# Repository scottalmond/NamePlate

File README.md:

# Name Plate Overview

Many cubicles are adorned with a standard aluminum name plate holding a piece of paper denoting the occupant's name.  This project presents an upgraded name tag that is backlit with LEDs.

This project was started as something simple to get active again after the COVID-19 lockdown.  Intent was to produce a visually engaging product with a price point at or below $25 in small production runs (10 units) to be in compliance with corporate gifting guidelines.

This unit employs nominally 100 WS2812B "NeoPixel" RGBW LEDs.  An ATtiny3216 was selected as a well supported processor (Arduino IDE) with a sizable flash memory (32kB).  To keep the design margin large, the SOIC package was selected.

The user can adjust the brightness of the unit through a potentiometer.  A Periphreal Touch Controller button allows quick user input while a hall effect sensor allows administrative functions.  A DIP switch allows for operation mode selection

# Assembled Unit

# Constituent Components

## Bill of Materials

## PCB

## Case

## Display Mask

## Face Plate

## Programmer

Direct referenced from: http://www.technoblogy.com/show?2OCH

- Install ElTangas's jtag2updi on Arduino Uno, Duemilanova or equivalent ATmega328p.  -- Details for making UPDI programmer: https://github.com/SpenceKonde/megaTinyCore/blob/master/MakeUPDIProgrammer.md
-- Use pin PD6 for UPDI I/O
- Install Spence Konde's megaTinyCore in the Arduino IDE
-- Instructions: https://github.com/SpenceKonde/megaTinyCore/blob/master/Installation.md
-- add to additional board URLs: http://drazzy.com/package_drazzy.com_index.json
-- boards manager add: "megaTinyCore" v2.0.5
- Upload settings:
-- Processor: ATtiny3216
-- 4.2 V BOD
-- 16 MHz
-- Programmer: jtag2updi

J8:
Pin 1: UPDI
Pin 2: +5V
Pin 6: GND

## Processor

doc: http://ww1.microchip.com/downloads/en/DeviceDoc/ATtiny3216-17-DataSheet-DS40002205A.pdf

# Periphreals

## DC Power

Note that this unit can sink substancial current.  It is recommended to power the unit with a 5V USB adapter capable of sourcing 2 Amps or more.

## LEDs [PA7]

## Touch Button [PB0]

Touching and releasing the very upper-left corner of the device for nominally 0.5 seconds will register a tap.  The unit will transition  between display patterns.

## Hall effect sensor [PA3]

Place a fridge or hard drive magnet just above the USB port.  This will activate <TBD function - implemented as fallback if PTC was problematic>

## Brightness Potentiometer [PA2]

Uncover the circuit board by removing the two thumb screws on either side of the faceplate.  Rotate the Philips potentiometer at the bottom left of the unit CW (?) to increase brightness.

## DIP Switch Settings [PA6, PA5, PA4]

Position 1:
Set to "OFF" to allow the displayed pattern to automaically update daily.  Set to "ON" to hold the currrently displayed pattern indefinitely.

Position 2:
Set to "ON" to configure the unit for collaboration mode.  In this mode the unit will communicate with other circuit boards to coordinate the displayed pattern.  For single PCB operation, the normal operation mode is "OFF".

Position 3:
Set to "ON" to enable diagnostic mode to allow verification and troublshooting of the user interfaces and outputs.  "OFF" is normal device operation.

Position 4:
Set to "ON" to connect the ID pin of the microUSB port to to the UPDI pin on the micro controller.  This is used for programming of the device without removing the circuit board from the casing.  "OFF" is normal operation.

# Collaboration Mode [PxD: PB2, RxD: PB3]

Multiple PCBs can be linked together to produce a larger display.  
<TBR>

# TODO

Add area for writing in owner name on PCB, for tracking units through development (if code differs)
Add CC BY 4.0 license to schematic
add year produced to PCB
>>> allow for batteyr power and power switch
>>> consider accel and swinging unit to create persistence of vision text display
add schematic links to readme.md
get solder paste with thinner tip
*** move micro USB header - difficult to reach for rework with config switches behind it (layout design issue)
note: LED is N/C in layout - why not flagged in DRc...?
b/c omitted connection in schematic due to copy-paste omission...
***fix D60 connection to 5V in next rev (schematic DRC issue)
-- run DRC in schematic too...
note: screw reads ~4V on delivery
magnet stuck at 0.87V despite exposure to hard drive magnet...
tried with pullup, still rigid at 0.87V
part is hot to the touch
note, the schematic part is AH1806 (hall switch) which has different pinout
- used this footprint because no footprint was supplied by vendor
*** next rev to swap pins 2 and 3 (schematic footprint issue)
consider testability point for EVERY IO
in user guide, include diagrams of expected UI screen output, ref 11.7V battery charger manual
include build number in start up script
compare findings on this CCA vs pendant which had button rotate 90 degrees (schematic footprint issue) and traces too close to holes (layout issue)
consider swapping hall effect sensor and brightness - allow greater accessibility to magnetic input
note:0.37" from LED-surface to top of programming header [note: 0.38" per data sheet, erxcluding solder]
contiguous undervolt - dim screen brighntess (LiPo response to dropping voltage)
min stackup (NO 1/16" acry): pcb 1.6 mm/0.063", 100 mil UPDI: 0.37", 0.125" acrylic face, 0.05" margin: 0.608"
max stackup (NO 1/16" acry): [5 turns 4-40 is 0.1250"] [50 mil backing], 200 mil standoff, 0.608" from above: 0.808"
min w/ 1/16 acry: 0.63+ above = 0.671"
max w/ 1/16 acry: 0.63+ above = 0.871"
note: thumb screw head 11/64" thick BEYOND base length above
0.75" is max length fully threaded.  next step up is 1"
note: head diameter on thumb screw is 5/16"
.75-1/8"+.05 back = 
box height at 0.8".  Add 1/16" when fabricating with acrylic
>>> enlarge PCB holes to be close fit.  Currently too small
allow for flipping vertically - flip flag, matrix rtain, etc
>>> consider moving silk screen contact info to behind a hole in the back of the unit
v1-0 --> v1-1 case:
50 mil WAS --> 100 mil IS margin inside pcb-to-case
50 mil WAS --> 150 mil IS wall thickness
WAS circle vent holes --> IS diamond vent holes --> will turn off supports
WAS 4x PCB holders, IS 2x PCB holders in the center
WAS NO chamfer inside unit --> IS chamfer around inner edge to provide wall support
WAS 4x faceplate holders --> IS NO facaeplate holders
WAS NO USB port --> IS USB PORT --> need dimensions of usb plug, and concern with unsupported 3d print
micro usb header metal = 0.07", 0.2" from opposing side of usb to verrtical case edge, 0.31" total
0.27" wide, 0.35" from opposing edge to case, 0.43" total
kicad center hole at 3.8" Y, 4.083" for microUSB port center
microUSB center 1.2 mm above surface of PCB
consider first boot (all 1's in EEPROM) to debug chaper.  First user input to change EEPROM exits hidden chapter
*** consider screw slots due to 3d print contraction
current draw?
leakage through usb port?
*** add lip to top edge to hide cut paper
consider standoffs (3d print?)
wasn't thinking about plastic contraction between ~10" separated holes
didn't think about light leakage through walls of solid plastic
note: the link from this pcb to others on the top/bottom has led pads very clodse to the power/ground rails
note: grips to hold pcb in place are non-effective (pcb too thin?)
consider pcb design features that allow for 2x rows of LEDs, NOT 4
didn't realize how short the final letts would be
debug screen: voltage, build #
1.8A at full brightness in full-screen mode (green colors)

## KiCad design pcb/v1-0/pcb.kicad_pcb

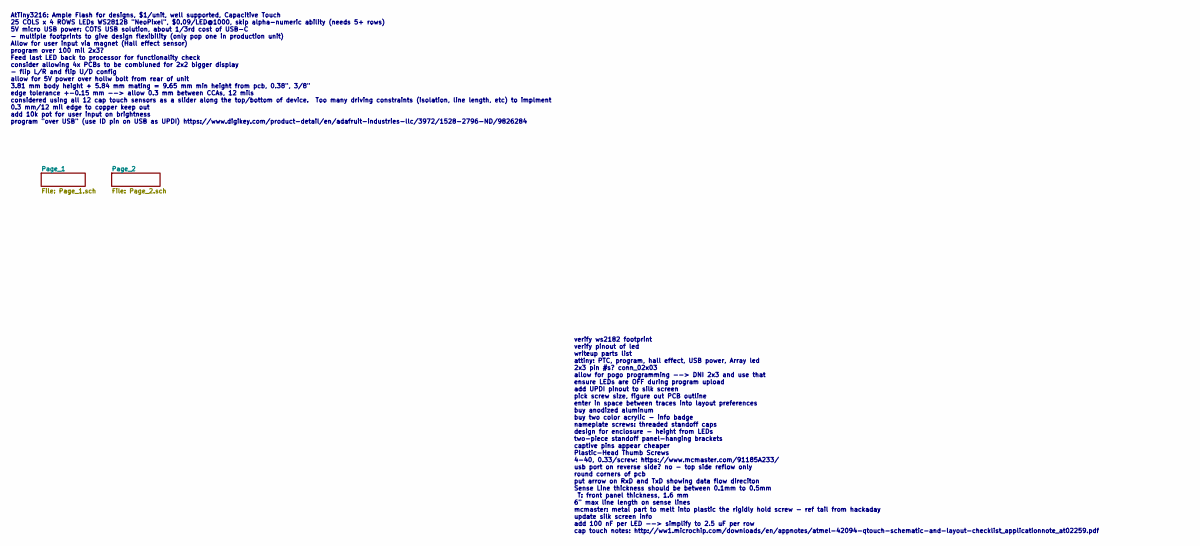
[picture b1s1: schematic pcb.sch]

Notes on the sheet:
verify ws2182 footprint verify pinout of led writeup parts list attiny: PTC, program, hall effect, USB power, Array led 2x3 pin #s? conn_02x03 allow for pogo programming --> DNI 2x3 and use that ensure LEDs are OFF during program upload add UPDI pinout to silk screen pick screw size, figure out PCB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
AtTiny3216: Ample Flash for designs, $1/unit, well supported, Capacitive Touch 25 COLS x 4 ROWS LEDs WS2812B "NeoPixel", $0.09/LED@1000, skip alpha-numeric ability (needs 5+ rows) 5V micro USB power: COTS USB solution, about 1/3rd cost of USB-C - multiple footprints to give design flexibility (only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

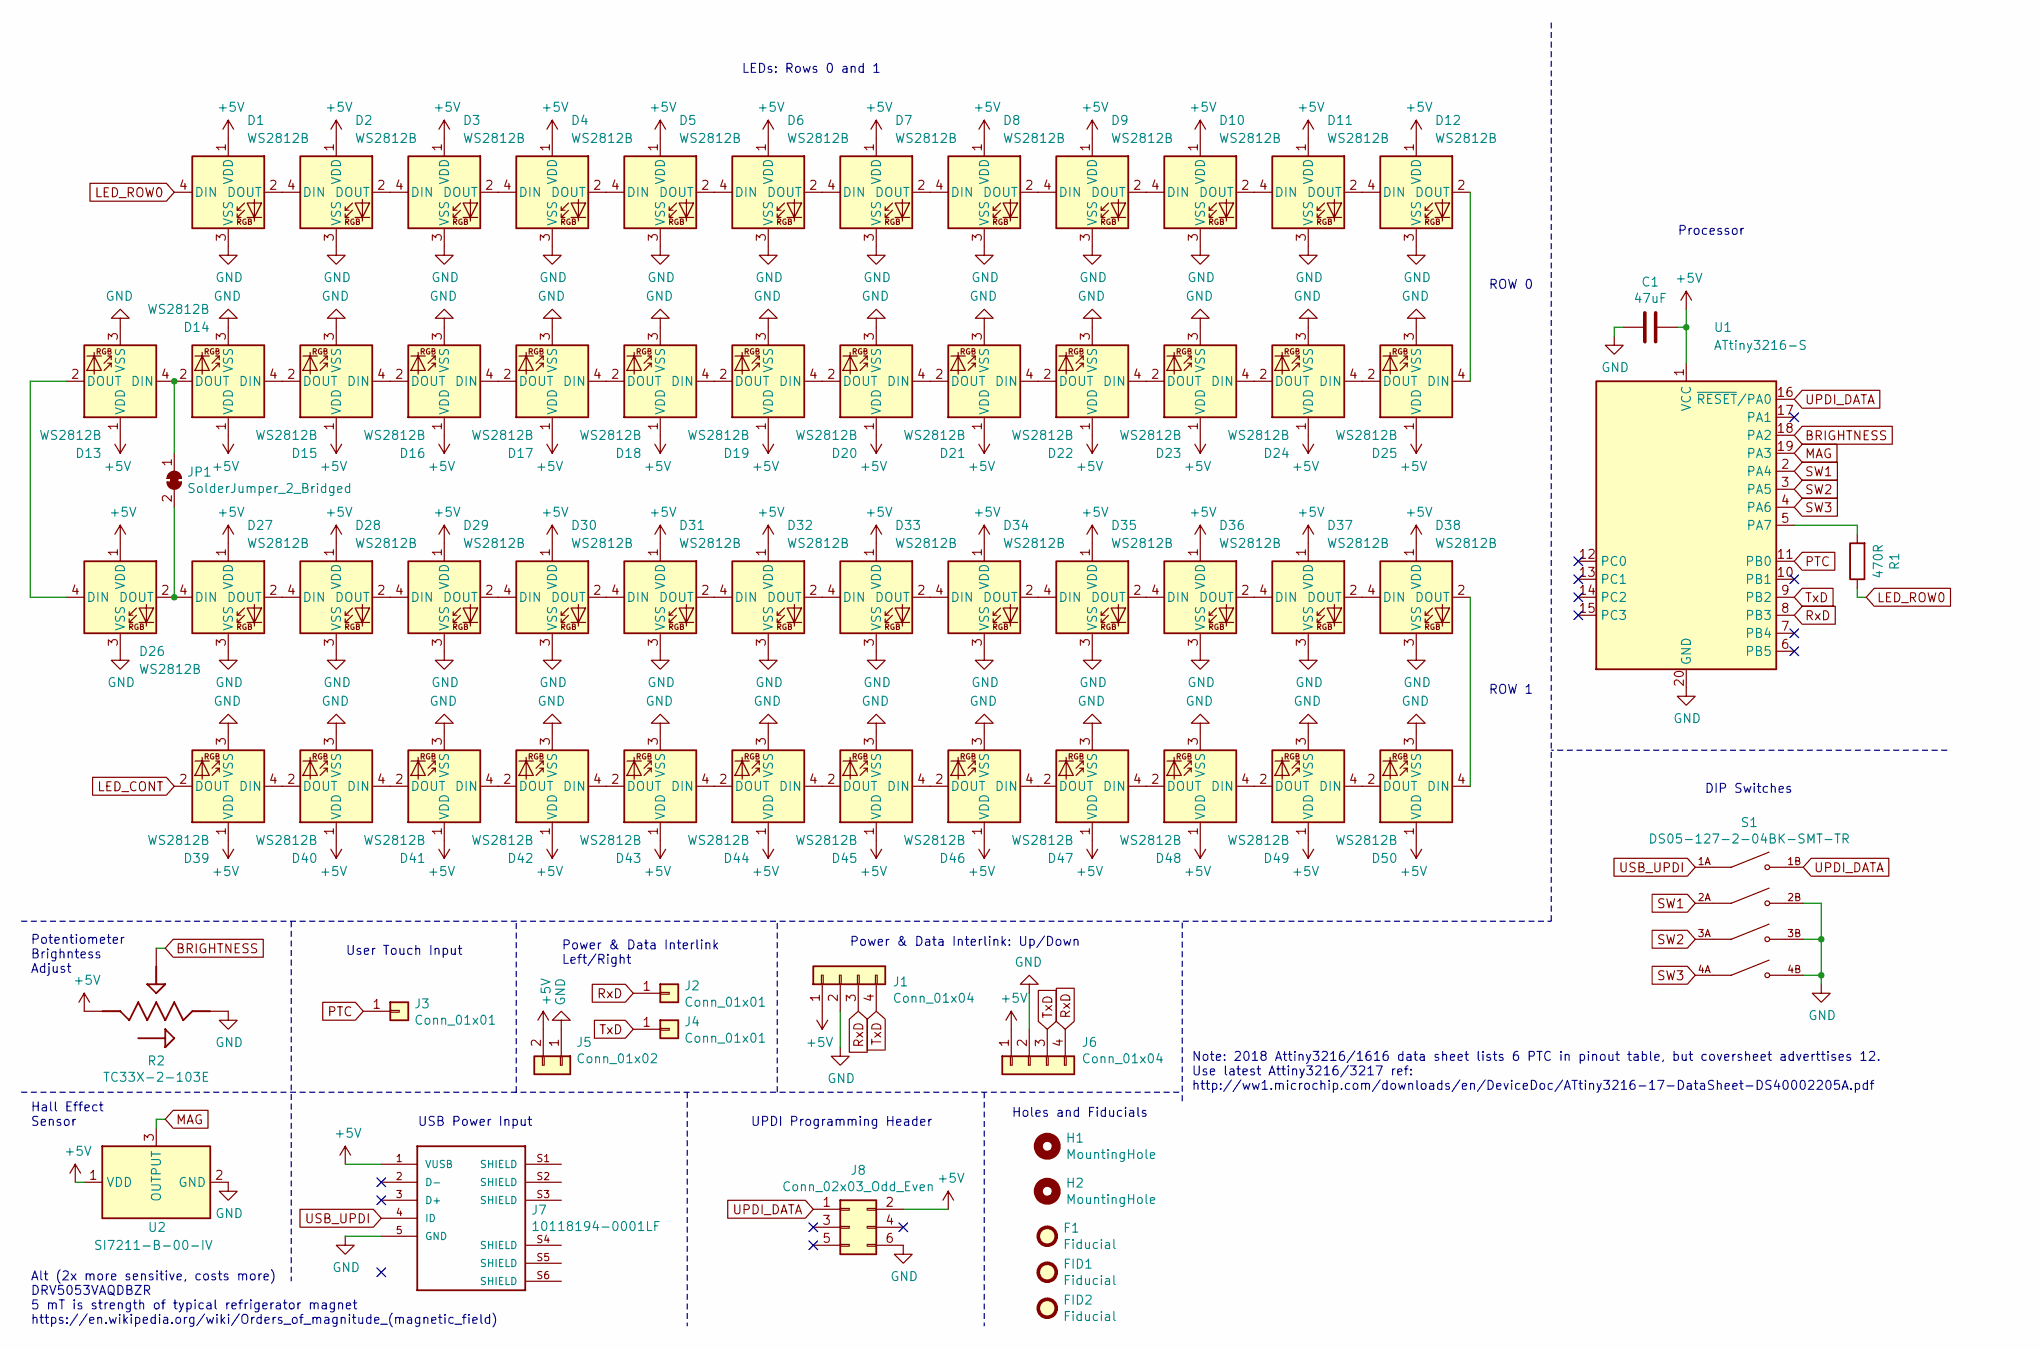
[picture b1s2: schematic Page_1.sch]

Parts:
C1: 47uF; C_0805_2012Metric
D1, D2, D3, D4, D5, D6, D7, D8, D9, D10, D11, D12, D13, D14, D15, D16, D17, D18, D19, D20, D21, D22, D23, D24, D25, D26, D27, D28, D29, D30, D31, D32, D33, D34, D35, D36, D37, D38, D39, D40, D41, D42, D43, D44, D45, D46, D47, D48, D49, D50: WS2812B; LED_WS2812B_PLCC4_5.0x5.0mm_P3.2mm
F1: Fiducial; Fiducial_1mm_Mask2mm
FID1, FID2: Fiducial; Fiducial_1mm_Mask2mm
H1, H2: MountingHole; MountingHole_2.5mm
J1, J6: Conn_01x04; PinHeader_1x04_P2.54mm_Vertical
J2, J4: Conn_01x01; PinHeader_1x01_P2.54mm_Vertical
J3: Conn_01x01; cap_touch
J5: Conn_01x02; PinHeader_1x02_P2.54mm_Vertical
J7: 10118194-0001LF; AMPHENOL_10118194-0001LF
J8: Conn_02x03_Odd_Even; PinHeader_2x03_P2.54mm_Vertical_SMD
JP1: SolderJumper_2_Bridged; SolderJumper-2_P1.3mm_Bridged_RoundedPad1.0x1.5mm
R1: 470R; R_0805_2012Metric
R2: TC33X-2-103E; 35WR
S1: DS05-127-2-04BK-SMT-TR; SW_DS05-127-2-04BK-SMT-TR
U1: ATtiny3216-S; SOIC-20W_7.5x12.8mm_P1.27mm
U2: SI7211-B-00-IV; SC-59

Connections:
+5V: C1.1, D1.1 (VDD), D2.1 (VDD), D3.1 (VDD), D4.1 (VDD), D5.1 (VDD), D6.1 (VDD), D7.1 (VDD), D8.1 (VDD), D9.1 (VDD), D10.1 (VDD), D11.1 (VDD), D12.1 (VDD), D13.1 (VDD), D14.1 (VDD), D15.1 (VDD), D16.1 (VDD), D17.1 (VDD), D18.1 (VDD), D19.1 (VDD), D20.1 (VDD), D21.1 (VDD), D22.1 (VDD), D23.1 (VDD), D24.1 (VDD), D25.1 (VDD), D26.1 (VDD), D27.1 (VDD), D28.1 (VDD), D29.1 (VDD), D30.1 (VDD), D31.1 (VDD), D32.1 (VDD), D33.1 (VDD), D34.1 (VDD), D35.1 (VDD), D36.1 (VDD), D37.1 (VDD), D38.1 (VDD), D39.1 (VDD), D40.1 (VDD), D41.1 (VDD), D42.1 (VDD), D43.1 (VDD), D44.1 (VDD), D45.1 (VDD), D46.1 (VDD), D47.1 (VDD), D48.1 (VDD), D49.1 (VDD), D50.1 (VDD), J1.1, J5.2, J6.1, J7.1 (VUSB), J8.2, R2.1, U1.1 (VCC), U2.1 (VDD); also elsewhere on the board
BRIGHTNESS: R2.2, U1.18 (PA2)
GND: C1.2, D1.3 (VSS), D2.3 (VSS), D3.3 (VSS), D4.3 (VSS), D5.3 (VSS), D6.3 (VSS), D7.3 (VSS), D8.3 (VSS), D9.3 (VSS), D10.3 (VSS), D11.3 (VSS), D12.3 (VSS), D13.3 (VSS), D14.3 (VSS), D15.3 (VSS), D16.3 (VSS), D17.3 (VSS), D18.3 (VSS), D19.3 (VSS), D20.3 (VSS), D21.3 (VSS), D22.3 (VSS), D23.3 (VSS), D24.3 (VSS), D25.3 (VSS), D26.3 (VSS), D27.3 (VSS), D28.3 (VSS), D29.3 (VSS), D30.3 (VSS), D31.3 (VSS), D32.3 (VSS), D33.3 (VSS), D34.3 (VSS), D35.3 (VSS), D36.3 (VSS), D37.3 (VSS), D38.3 (VSS), D39.3 (VSS), D40.3 (VSS), D41.3 (VSS), D42.3 (VSS), D43.3 (VSS), D44.3 (VSS), D45.3 (VSS), D46.3 (VSS), D47.3 (VSS), D48.3 (VSS), D49.3 (VSS), D50.3 (VSS), J1.2, J5.1, J6.2, J7.5 (GND), J8.6, R2.3, S1.2B, S1.3B, S1.4B, U1.20 (GND), U2.2 (GND); also elsewhere on the board
LED_CONT: D39.2 (DOUT); also elsewhere on the board
LED_ROW0: D1.4 (DIN), R1.1; also elsewhere on the board
MAG: U1.19 (PA3), U2.3 (OUTPUT)
unnamed: D1.2 (DOUT), D2.4 (DIN)
unnamed: D2.2 (DOUT), D3.4 (DIN)
unnamed: D3.2 (DOUT), D4.4 (DIN)
unnamed: D4.2 (DOUT), D5.4 (DIN)
unnamed: D5.2 (DOUT), D6.4 (DIN)
unnamed: D6.2 (DOUT), D7.4 (DIN)
unnamed: D7.2 (DOUT), D8.4 (DIN)
unnamed: D8.2 (DOUT), D9.4 (DIN)
unnamed: D10.2 (DOUT), D11.4 (DIN)
unnamed: D9.2 (DOUT), D10.4 (DIN)
unnamed: D11.2 (DOUT), D12.4 (DIN)
unnamed: D12.2 (DOUT), D25.4 (DIN)
unnamed: D13.2 (DOUT), D26.4 (DIN)
unnamed: D13.4 (DIN), D14.2 (DOUT), JP1.1 (A)
unnamed: D14.4 (DIN), D15.2 (DOUT)
unnamed: D15.4 (DIN), D16.2 (DOUT)
unnamed: D16.4 (DIN), D17.2 (DOUT)
unnamed: D17.4 (DIN), D18.2 (DOUT)
unnamed: D18.4 (DIN), D19.2 (DOUT)
unnamed: D19.4 (DIN), D20.2 (DOUT)
unnamed: D20.4 (DIN), D21.2 (DOUT)
unnamed: D21.4 (DIN), D22.2 (DOUT)
unnamed: D22.4 (DIN), D23.2 (DOUT)
unnamed: D23.4 (DIN), D24.2 (DOUT)
unnamed: D24.4 (DIN), D25.2 (DOUT)
unnamed: D26.2 (DOUT), D27.4 (DIN), JP1.2 (B)
unnamed: D27.2 (DOUT), D28.4 (DIN)
unnamed: D28.2 (DOUT), D29.4 (DIN)
unnamed: D29.2 (DOUT), D30.4 (DIN)
unnamed: D30.2 (DOUT), D31.4 (DIN)
unnamed: D31.2 (DOUT), D32.4 (DIN)
unnamed: D32.2 (DOUT), D33.4 (DIN)
unnamed: D33.2 (DOUT), D34.4 (DIN)
unnamed: D34.2 (DOUT), D35.4 (DIN)
unnamed: D35.2 (DOUT), D36.4 (DIN)
unnamed: D36.2 (DOUT), D37.4 (DIN)
unnamed: D37.2 (DOUT), D38.4 (DIN)
unnamed: D38.2 (DOUT), D50.4 (DIN)
unnamed: D39.4 (DIN), D40.2 (DOUT)
unnamed: D40.4 (DIN), D41.2 (DOUT)
unnamed: D41.4 (DIN), D42.2 (DOUT)
unnamed: D42.4 (DIN), D43.2 (DOUT)
unnamed: D43.4 (DIN), D44.2 (DOUT)
unnamed: D44.4 (DIN), D45.2 (DOUT)
unnamed: D45.4 (DIN), D46.2 (DOUT)
unnamed: D46.4 (DIN), D47.2 (DOUT)
unnamed: D47.4 (DIN), D48.2 (DOUT)
unnamed: D48.4 (DIN), D49.2 (DOUT)
unnamed: D49.4 (DIN), D50.2 (DOUT)
unnamed: R1.2, U1.5 (PA7)
PTC: J3.1, U1.11 (PB0)
RxD: J1.3, J2.1, J6.4, U1.8 (PB3)
SW2: S1.3A, U1.3 (PA5)
TxD: J1.4, J4.1, J6.3, U1.9 (PB2)
UPDI_DATA: J8.1, S1.1B, U1.16 (~RESET~/PA0)
USB_UPDI: J7.4 (ID), S1.1A

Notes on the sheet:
UPDI Programming Header
Note: 2018 Attiny3216/1616 data sheet lists 6 PTC in pinout table, but coversheet adverttises 12. Use latest Attiny3216/3217 ref: http://ww1.microchip.com/downloads/en/DeviceDoc/ATtiny3216-17-DataSheet-DS40002205A.pdf
Alt (2x more sensitive, costs more) DRV5053VAQDBZR 5 mT is strength of typical refrigerator magnet https://en.wikipedia.org/wiki/Orders_of_magnitude_(magnetic_field)
Power & Data Interlink Left/Right
Power & Data Interlink: Up/Down
USB Power Input
User Touch Input
Potentiometer Brighntess Adjust
Holes and Fiducials
Processor
LEDs: Rows 0 and 1
ROW 0
ROW 1
Hall Effect Sensor
DIP Switches

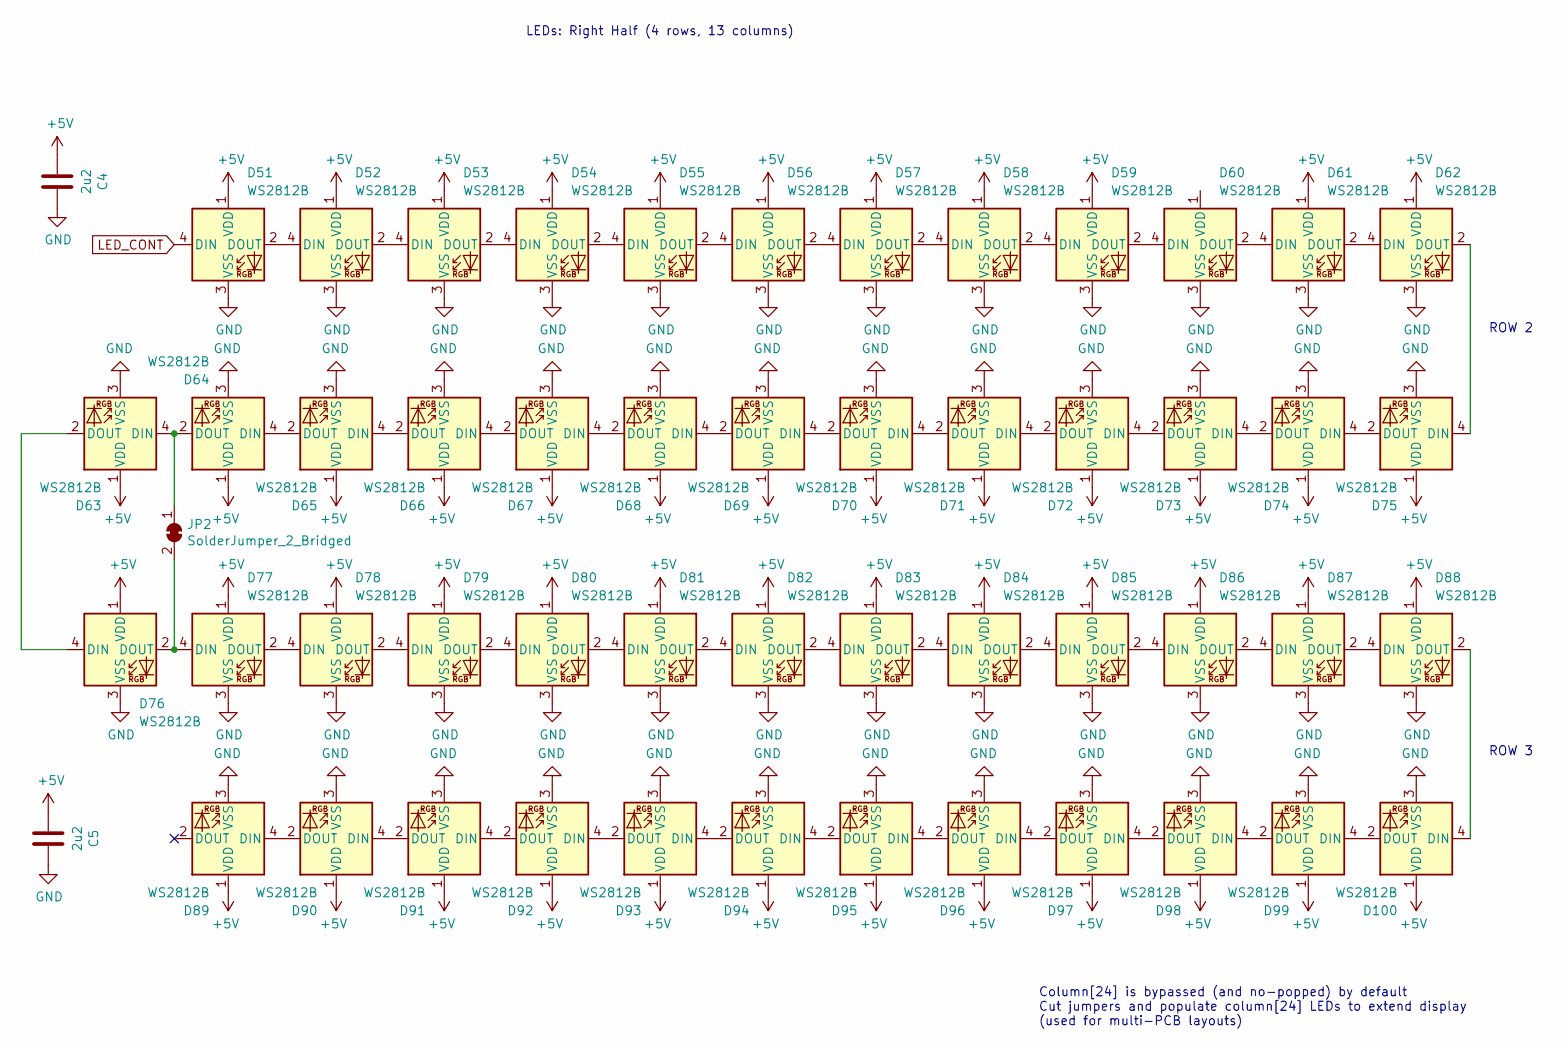
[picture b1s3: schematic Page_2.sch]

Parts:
C4, C5: 2u2; C_0805_2012Metric
D51, D52, D53, D54, D55, D56, D57, D58, D59, D60, D61, D62, D63, D64, D65, D66, D67, D68, D69, D70, D71, D72, D73, D74, D75, D76, D77, D78, D79, D80, D81, D82, D83, D84, D85, D86, D87, D88, D89, D90, D91, D92, D93, D94, D95, D96, D97, D98, D99, D100: WS2812B; LED_WS2812B_PLCC4_5.0x5.0mm_P3.2mm
JP2: SolderJumper_2_Bridged; SolderJumper-2_P1.3mm_Bridged_RoundedPad1.0x1.5mm

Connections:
+5V: C4.2, C5.2, D51.1 (VDD), D52.1 (VDD), D53.1 (VDD), D54.1 (VDD), D55.1 (VDD), D56.1 (VDD), D57.1 (VDD), D58.1 (VDD), D59.1 (VDD), D61.1 (VDD), D62.1 (VDD), D63.1 (VDD), D64.1 (VDD), D65.1 (VDD), D66.1 (VDD), D67.1 (VDD), D68.1 (VDD), D69.1 (VDD), D70.1 (VDD), D71.1 (VDD), D72.1 (VDD), D73.1 (VDD), D74.1 (VDD), D75.1 (VDD), D76.1 (VDD), D77.1 (VDD), D78.1 (VDD), D79.1 (VDD), D80.1 (VDD), D81.1 (VDD), D82.1 (VDD), D83.1 (VDD), D84.1 (VDD), D85.1 (VDD), D86.1 (VDD), D87.1 (VDD), D88.1 (VDD), D89.1 (VDD), D90.1 (VDD), D91.1 (VDD), D92.1 (VDD), D93.1 (VDD), D94.1 (VDD), D95.1 (VDD), D96.1 (VDD), D97.1 (VDD), D98.1 (VDD), D99.1 (VDD), D100.1 (VDD); also elsewhere on the board
GND: C4.1, C5.1, D51.3 (VSS), D52.3 (VSS), D53.3 (VSS), D54.3 (VSS), D55.3 (VSS), D56.3 (VSS), D57.3 (VSS), D58.3 (VSS), D59.3 (VSS), D60.3 (VSS), D61.3 (VSS), D62.3 (VSS), D63.3 (VSS), D64.3 (VSS), D65.3 (VSS), D66.3 (VSS), D67.3 (VSS), D68.3 (VSS), D69.3 (VSS), D70.3 (VSS), D71.3 (VSS), D72.3 (VSS), D73.3 (VSS), D74.3 (VSS), D75.3 (VSS), D76.3 (VSS), D77.3 (VSS), D78.3 (VSS), D79.3 (VSS), D80.3 (VSS), D81.3 (VSS), D82.3 (VSS), D83.3 (VSS), D84.3 (VSS), D85.3 (VSS), D86.3 (VSS), D87.3 (VSS), D88.3 (VSS), D89.3 (VSS), D90.3 (VSS), D91.3 (VSS), D92.3 (VSS), D93.3 (VSS), D94.3 (VSS), D95.3 (VSS), D96.3 (VSS), D97.3 (VSS), D98.3 (VSS), D99.3 (VSS), D100.3 (VSS); also elsewhere on the board
LED_CONT: D51.4 (DIN); also elsewhere on the board
unnamed: D51.2 (DOUT), D52.4 (DIN)
unnamed: D52.2 (DOUT), D53.4 (DIN)
unnamed: D53.2 (DOUT), D54.4 (DIN)
unnamed: D54.2 (DOUT), D55.4 (DIN)
unnamed: D55.2 (DOUT), D56.4 (DIN)
unnamed: D56.2 (DOUT), D57.4 (DIN)
unnamed: D57.2 (DOUT), D58.4 (DIN)
unnamed: D58.2 (DOUT), D59.4 (DIN)
unnamed: D59.2 (DOUT), D60.4 (DIN)
unnamed: D60.2 (DOUT), D61.4 (DIN)
unnamed: D61.2 (DOUT), D62.4 (DIN)
unnamed: D62.2 (DOUT), D75.4 (DIN)
unnamed: D63.2 (DOUT), D76.4 (DIN)
unnamed: D63.4 (DIN), D64.2 (DOUT), JP2.1 (A)
unnamed: D64.4 (DIN), D65.2 (DOUT)
unnamed: D65.4 (DIN), D66.2 (DOUT)
unnamed: D66.4 (DIN), D67.2 (DOUT)
unnamed: D67.4 (DIN), D68.2 (DOUT)
unnamed: D68.4 (DIN), D69.2 (DOUT)
unnamed: D69.4 (DIN), D70.2 (DOUT)
unnamed: D70.4 (DIN), D71.2 (DOUT)
unnamed: D71.4 (DIN), D72.2 (DOUT)
unnamed: D72.4 (DIN), D73.2 (DOUT)
unnamed: D73.4 (DIN), D74.2 (DOUT)
unnamed: D74.4 (DIN), D75.2 (DOUT)
unnamed: D76.2 (DOUT), D77.4 (DIN), JP2.2 (B)
unnamed: D77.2 (DOUT), D78.4 (DIN)
unnamed: D78.2 (DOUT), D79.4 (DIN)
unnamed: D79.2 (DOUT), D80.4 (DIN)
unnamed: D80.2 (DOUT), D81.4 (DIN)
unnamed: D81.2 (DOUT), D82.4 (DIN)
unnamed: D82.2 (DOUT), D83.4 (DIN)
unnamed: D83.2 (DOUT), D84.4 (DIN)
unnamed: D84.2 (DOUT), D85.4 (DIN)
unnamed: D85.2 (DOUT), D86.4 (DIN)
unnamed: D86.2 (DOUT), D87.4 (DIN)
unnamed: D87.2 (DOUT), D88.4 (DIN)
unnamed: D89.4 (DIN), D90.2 (DOUT)
unnamed: D90.4 (DIN), D91.2 (DOUT)
unnamed: D91.4 (DIN), D92.2 (DOUT)
unnamed: D92.4 (DIN), D93.2 (DOUT)
unnamed: D93.4 (DIN), D94.2 (DOUT)
unnamed: D94.4 (DIN), D95.2 (DOUT)
unnamed: D95.4 (DIN), D96.2 (DOUT)
unnamed: D96.4 (DIN), D97.2 (DOUT)
unnamed: D97.4 (DIN), D98.2 (DOUT)
unnamed: D98.4 (DIN), D99.2 (DOUT)
unnamed: D99.4 (DIN), D100.2 (DOUT)
unnamed: D88.2 (DOUT), D100.4 (DIN)

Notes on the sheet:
Column[24] is bypassed (and no-popped) by default Cut jumpers and populate column[24] LEDs to extend display (used for multi-PCB layouts)
LEDs: Right Half (4 rows, 13 columns)
ROW 2
ROW 3

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
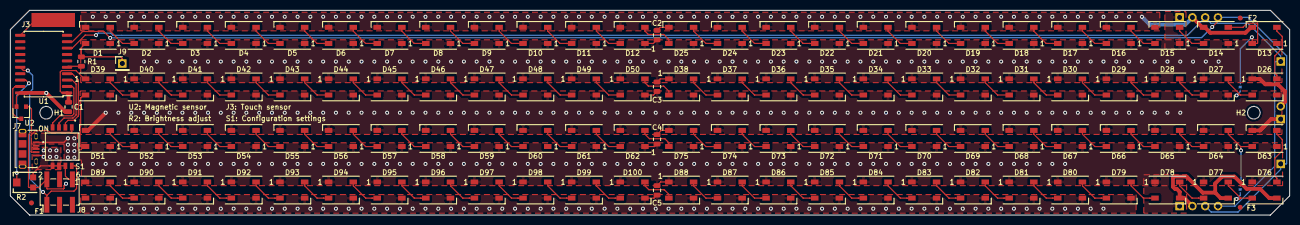
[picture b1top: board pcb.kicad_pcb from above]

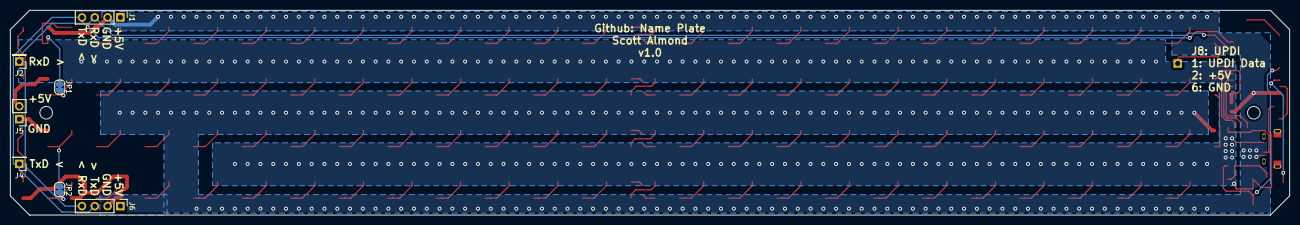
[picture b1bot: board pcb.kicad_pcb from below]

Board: 2 copper layers, 254.0 x 40.6 mm, 126 parts (7 on the bottom side), 113 nets.

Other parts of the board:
C2, C3: 2u2; C_0805_2012Metric
F2, F3: Fiducial; Fiducial_1mm_Mask2mm
J9: Conn_01x01; PinHeader_1x01_P2.54mm_Vertical

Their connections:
+5V: C2.2, C3.2; also elsewhere on the board
GND: C2.1, C3.1; also elsewhere on the board
LED_ROW0: J9.1; also elsewhere on the board

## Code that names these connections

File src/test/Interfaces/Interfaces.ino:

/*
  Blink

  Turns an LED on for one second, then off for one second, repeatedly.

  Most Arduinos have an on-board LED you can control. On the UNO, MEGA and ZERO
  it is attached to digital pin 13, on MKR1000 on pin 6. LED_BUILTIN is set to
  the correct LED pin independent of which board is used.
  If you want to know what pin the on-board LED is connected to on your Arduino
  model, check the Technical Specs of your board at:
  https://www.arduino.cc/en/Main/Products

  modified 8 May 2014
  by Scott Fitzgerald
  modified 2 Sep 2016
  by Arturo Guadalupi
  modified 8 Sep 2016
  by Colby Newman

  This example code is in the public domain.

  http://www.arduino.cc/en/Tutorial/Blink
*/

#include <Adafruit_NeoPixel.h>
#ifdef __AVR__
 #include <avr/power.h> // Required for 16 MHz Adafruit Trinket
#endif

const byte PIN_LED=PIN_PA7;
const byte LED_COUNT=96;
//note: with large LED counts, the show() method, which disables interrupts, will miss milliseconds
//interrupts.  The millis() method will no longer update properly
//100 LEDs loses about ~2 ms interrupts every call:to show() https://forums.adafruit.com/viewtopic.php?f=47&t=42720
//micros() has the same issue https://roboticsbackend.com/arduino-millis-vs-micros/
//future: consider combination of LED_COUNT, millis() and micros() to compensate for the microseconds needed
neoPixelType STRIP_TYPE=NEO_GRBW + NEO_KHZ800;
Adafruit_NeoPixel strip = Adafruit_NeoPixel(LED_COUNT, PIN_LED, STRIP_TYPE);

const byte PIN_TOUCH=PIN_PB0;//periphreal touch controller button
const byte PIN_MAGNET=PIN_PA3;
const byte PIN_BRIGHTNESS=PIN_PA2;
const byte PIN_CONFIG_UPDATE_DAILY=PIN_PA6;//SW2 on DIP switch
const byte PIN_CONFIG_DIAGNOSTIC=PIN_PA5;//SW3 on DIP switch
const byte PIN_CONFIG_TESSELLATE=PIN_PA4;//SW4 on DIP switch
//note: SW1 is used for programming UPDI pin over the ID pin of the USB input

// the setup function runs once when you press reset or power the board
void setup() {
  // initialize digital pin LED_BUILTIN as an output.
  pinMode(PIN_LED, OUTPUT);
  pinMode(PIN_CONFIG_UPDATE_DAILY,INPUT_PULLUP);
  pinMode(PIN_CONFIG_DIAGNOSTIC,INPUT_PULLUP);
  pinMode(PIN_CONFIG_TESSELLATE,INPUT_PULLUP);
  strip.begin();
  strip.setBrightness(4);
  strip.clear();
}

// the loop function runs over and over again forever
void loop() {
  //testLED0(true);
  //testStripWhite();
  testStripCounter();
  //testMagnet();
  //testBrightness();
}

void testLED0(bool isShow)
{
  if((millis() >> 11) % 2)
  {
    uint16_t hue=millis()*8*4;//set higher multiplication to cycle LEDs faster.  *16 is cycling full rainbow every ~8 seconds
    uint8_t  sat = 255;
    uint8_t  val = 255 ;
    strip.setPixelColor(0, strip.gamma32(strip.ColorHSV(hue, sat, val)));
  }else{
    uint16_t val=millis()*32*4;
    if(val&0x8000) val=255-((val>>7)&0x00FF);
    else val=(val>>7)&0x00FF;
    strip.setPixelColor(0, strip.Color(0,0,0,val));
  }
  if(isShow) strip.show();
}

void testStripWhite()
{//one white pixels walks through all LEDs
  strip.clear();
  byte iter=(millis()/64)%LED_COUNT;
  strip.setPixelColor(iter, strip.Color(0,0,0,255));
  strip.show();
}

void testStripCounter()
{
  strip.clear();
  for(byte iter=0;iter<((millis()/64)%(LED_COUNT+1));iter++)
  {
    strip.setPixelColor(iter, strip.Color(0,0,0,255));
  }
  testLED0(false);
  strip.show();
}

void testMagnet()
{
  strip.clear();
  for(byte iter=0;iter<readMagnetism()/4;iter++)
  {
    strip.setPixelColor(iter, strip.Color(0,0,0,255));
  }
  strip.show();
}

void testBrightness()
{
  strip.clear();
  for(byte iter=0;iter<readBrightness()/8;iter++)
  {
    strip.setPixelColor(iter, strip.Color(0,0,0,255));
  }
  strip.show();
}

void testSwitches()
{
  
}

//read the 10-bit ADC to get analog measurements: brightness configuration and magnet
word readMagnetism(){  return analogRead(PIN_MAGNET);     }
word readBrightness(){ return analogRead(PIN_BRIGHTNESS); }//getBrightness is already defined in LED library
//read touch button...

//read config settings
bool isUpdateDaily(){    return digitalRead(PIN_CONFIG_UPDATE_DAILY); }
bool isDiagnosticMode(){ return digitalRead(PIN_CONFIG_DIAGNOSTIC);   }
bool isTessellateMOde(){ return digitalRead(PIN_CONFIG_TESSELLATE);   }

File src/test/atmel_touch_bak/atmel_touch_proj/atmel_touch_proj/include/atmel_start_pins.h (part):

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#include <port.h>

/**
 * \brief Set PIN_PA7 pull mode
 *
 * Configure pin to pull up, down or disable pull mode, supported pull
 * modes are defined by device used
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}

/**
 * \brief Set PIN_PA7 data direction
 *
 * Select if the pin data direction is input, output or disabled.
 * If disabled state is not possible, this function throws an assert.
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}

/**
 * \brief Set PIN_PA7 input/sense configuration
 *
 * Enable/disable PIN_PA7 digital input buffer and pin change interrupt,
 * select pin interrupt edge/level sensing mode
 *
 * \param[in] isc PORT_ISC_INTDISABLE_gc    = Iterrupt disabled but input buffer enabled
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}

/**
 * \brief Set PIN_PA7 inverted mode
 *
 * Enable or disable inverted I/O on a pin
 *
 * \param[in] inverted true  = I/O on PIN_PA7 is inverted
 *                     false = I/O on PIN_PA7 is not inverted
 */
static inline void PIN_PA7_set_inverted(const bool inverted)
{
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}

/**
 * \brief Set PIN_PA7 level
 *
 * Sets output level on a pin
 *
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}

/**
 * \brief Toggle output level on PIN_PA7
 *
 * Toggle the pin level
 */
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}

/**
 * \brief Get level on PIN_PA7
 *
 * Reads the level on a pin
 */
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}

/**
 * \brief Set PIN_PB0 pull mode
 *
 * Configure pin to pull up, down or disable pull mode, supported pull
 * modes are defined by device used
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}

/**
 * \brief Set PIN_PB0 data direction
 *
 * Select if the pin data direction is input, output or disabled.
 * If disabled state is not possible, this function throws an assert.
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}

/**
 * \brief Set PIN_PB0 input/sense configuration
 *
 * Enable/disable PIN_PB0 digital input buffer and pin change interrupt,
 * select pin interrupt edge/level sensing mode
 *
 * \param[in] isc PORT_ISC_INTDISABLE_gc    = Iterrupt disabled but input buffer enabled
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}

/**
 * \brief Set PIN_PB0 inverted mode
 *
 * Enable or disable inverted I/O on a pin
 *
 * \param[in] inverted true  = I/O on PIN_PB0 is inverted
 *                     false = I/O on PIN_PB0 is not inverted
 */
static inline void PIN_PB0_set_inverted(const bool inverted)
{
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}

/**
 * \brief Set PIN_PB0 level
 *
 * Sets output level on a pin
 *
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}

/**
 * \brief Toggle output level on PIN_PB0
 *
 * Toggle the pin level
 */
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}

/**
 * \brief Get level on PIN_PB0
 *
 * Reads the level on a pin
 */
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}

/**
 * \brief Set PB2 pull mode
 *
 * Configure pin to pull up, down or disable pull mode, supported pull
 * modes are defined by device used
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}

/**
 * \brief Set PB2 data direction
 *
 * Select if the pin data direction is input, output or disabled.
 * If disabled state is not possible, this function throws an assert.
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}

/**
 * \brief Set PB2 input/sense configuration
 *
 * Enable/disable PB2 digital input buffer and pin change interrupt,
 * select pin interrupt edge/level sensing mode
 *
 * \param[in] isc PORT_ISC_INTDISABLE_gc    = Iterrupt disabled but input buffer enabled
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}

/**
 * \brief Set PB2 inverted mode
 *
 * Enable or disable inverted I/O on a pin
 *
 * \param[in] inverted true  = I/O on PB2 is inverted
 *                     false = I/O on PB2 is not inverted
 */
static inline void PB2_set_inverted(const bool inverted)
{
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}

/**
 * \brief Set PB2 level
 *
 * Sets output level on a pin
 *
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}

/**
 * \brief Toggle output level on PB2
 *
 * Toggle the pin level
 */
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}

/**
 * \brief Get level on PB2
 *
 * Reads the level on a pin
 */
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}

/**
 * \brief Set PB3 pull mode
 *
 * Configure pin to pull up, down or disable pull mode, supported pull
 * modes are defined by device used
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}

/**
 * \brief Set PB3 data direction
 *
 * Select if the pin data direction is input, output or disabled.
 * If disabled state is not possible, this function throws an assert.
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}

/**
 * \brief Set PB3 input/sense configuration
 *
 * Enable/disable PB3 digital input buffer and pin change interrupt,
 * select pin interrupt edge/level sensing mode
 *
 * \param[in] isc PORT_ISC_INTDISABLE_gc    = Iterrupt disabled but input buffer enabled
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}

/**
 * \brief Set PB3 inverted mode
 *
 * Enable or disable inverted I/O on a pin
 *
 * \param[in] inverted true  = I/O on PB3 is inverted
 *                     false = I/O on PB3 is not inverted
 */
static inline void PB3_set_inverted(const bool inverted)
{
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}

/**
 * \brief Set PB3 level
 *
 * Sets output level on a pin
 *
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}

/**
 * \brief Toggle output level on PB3
 *
 * Toggle the pin level
 */
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}

/**
 * \brief Get level on PB3
 *
 * Reads the level on a pin
 */
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
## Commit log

2020-07-12 initial
2020-07-12 copy-paste LEDs in schematic
2020-07-12 link schematic leds to layout
2020-07-12 consider program over custom USB and remove 100 mil UPDI header
2020-07-12 compontnets placedr
2020-07-13 pre-zone fill
2020-07-14 candidate draft
2020-07-15 v1.0 as ordered
2020-07-16 filling in documentation
2020-07-18 case draft
2020-07-23 first build findings
2020-07-26 reinstall arduino ide where atmel studio can find it
2020-07-27 stencil ordered
2020-07-27 thumb screws ordered
2020-07-28 rainbow ripple implemented
2020-07-29 generated stl and front panel pdf
2020-07-29 fixed vent hole size being too large
2020-07-29 candidate meteor build
2020-07-31 added chamfer
2020-07-31 added vent holes
2020-07-31 removed face plate suports - no longer needed
2020-07-31 finializing build 1-1
2020-08-01 fix obj and stl export
2020-08-03 lengthen mounting holes
2020-08-04 production build 1-0
2020-08-25 image upload
2020-08-28 fix dimensions and font in text template
